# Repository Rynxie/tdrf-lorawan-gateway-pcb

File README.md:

# Open-Source Linux-Based LoRaWAN Gateway

A custom-designed, open-source **LoRaWAN gateway PCB** powered by the **Allwinner V3s ARM Cortex-A7 processor** and the **Semtech SX1302 LoRa concentrator**.

The gateway combines custom hardware with an embedded Linux software stack built using Buildroot, providing a flexible platform for LoRaWAN communication and IoT applications.

## Hardware Prototypes

Two assembled and tested LoRaWAN gateway prototypes.

| Assembled Gateway | PCB Component Layout |
|---|---|
|  |  |

## Project Overview

This project focuses on designing and developing a standalone Linux-based LoRaWAN gateway, including both custom PCB hardware and embedded Linux firmware.

The gateway was developed under the **TÜBİTAK 2209-A Undergraduate Research Projects Support Program** and subsequently integrated into the **LoRa-Based Low-Power Tracking System for Critical Cargo**, supported by the **Turkish Aerospace Industries LIFT UP Graduation Project Support Program**.

## Hardware

The hardware was designed in **KiCad**, integrating the processing unit, LoRa concentrator, RF transceivers, and peripheral interfaces on a custom PCB.

### Main Components

| Component | Description |
|---|---|
| Allwinner V3s | ARM Cortex-A7 MPU with integrated 64 MB DDR2 RAM |
| Semtech SX1302 | LoRa Core digital baseband concentrator |
| Semtech SX1250 | LoRa RF transceivers |
| Ethernet | Wired network connectivity |
| Quectel L86 | GNSS module |
| USB Type-C | USB interface |
| Custom PCB | Integrated gateway hardware platform |

## Embedded Linux Software

The gateway runs a customized embedded Linux distribution generated using **Buildroot**.

The software environment includes:

- **Linux Kernel:** Customized for the Allwinner V3s hardware platform
- **BusyBox:** Lightweight userspace utilities
- **Semtech UDP Packet Forwarder:** Forwarding LoRa packets to a network server
- **ChirpStack:** LoRaWAN Network Server integration

### System Architecture

```text
        LoRaWAN End Devices
                 |
                 | LoRa RF
                 v
       +-------------------+
       | Semtech SX1250    |
       | RF Transceivers   |
       +---------+---------+
                 |
                 v
       +-------------------+
       | Semtech SX1302    |
       | LoRa Concentrator |
       +---------+---------+
                 |
                 | SPI
                 v
       +-------------------+
       | Allwinner V3s     |
       | Embedded Linux    |
       | Buildroot         |
       | Packet Forwarder  |
       +---------+---------+
                 |
                 | Ethernet
                 v
       +-------------------+
       | ChirpStack        |
       | LoRaWAN Network   |
       | Server            |
       +-------------------+
```

## Testing and Validation

Two final hardware prototypes were manufactured, assembled, and tested.

The gateway was integrated into a LoRa-based low-power tracking system for critical cargo, providing a practical environment for evaluating the custom hardware and embedded Linux software.

We reached up to **1 km** distance in a urban area and looking for ways to increase the range

## Repository Contents

This repository focuses on the **hardware design** of the LoRaWAN gateway.

It contains the KiCad project and associated hardware design resources, including:

- PCB schematic
- PCB layout
- Component symbols and footprints
- Manufacturing and production files

## Project Team

- **Tunahan Kaya** — Embedded Linux and software development
- **Dilara Tatar** — Hardware development
- **Dr. Yalçın Albayrak** — Academic advisor

## Acknowledgments

This project was supported by the **TÜBİTAK 2209-A Undergraduate Research Projects Support Program**.

The gateway was also integrated and tested within a project supported by the **TUSAŞ LIFT UP Graduation Project Support Program**.

Special thanks to the project team and our academic advisor for their contributions and support throughout the development process.

## References

- [GitHub Repository](https://github.com/Rynxie/tdrf-lorawan-gateway-pcb)
- [Original LinkedIn Post](https://lnkd.in/p/d-5i6TTB)

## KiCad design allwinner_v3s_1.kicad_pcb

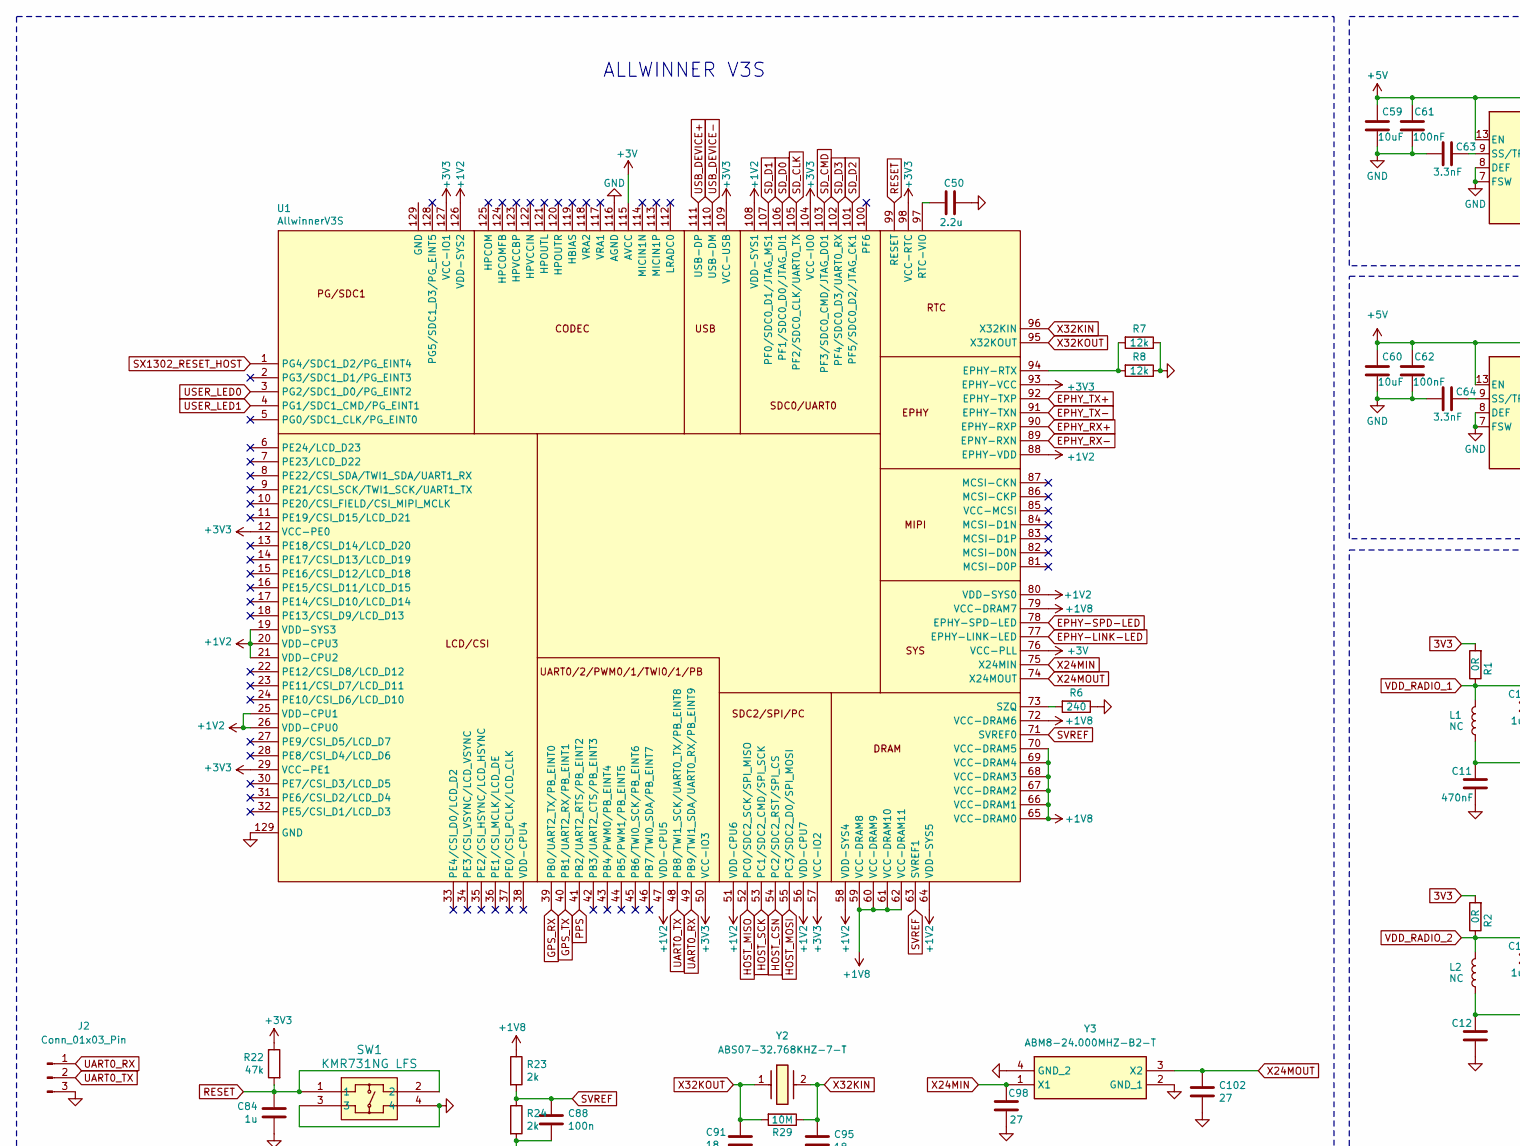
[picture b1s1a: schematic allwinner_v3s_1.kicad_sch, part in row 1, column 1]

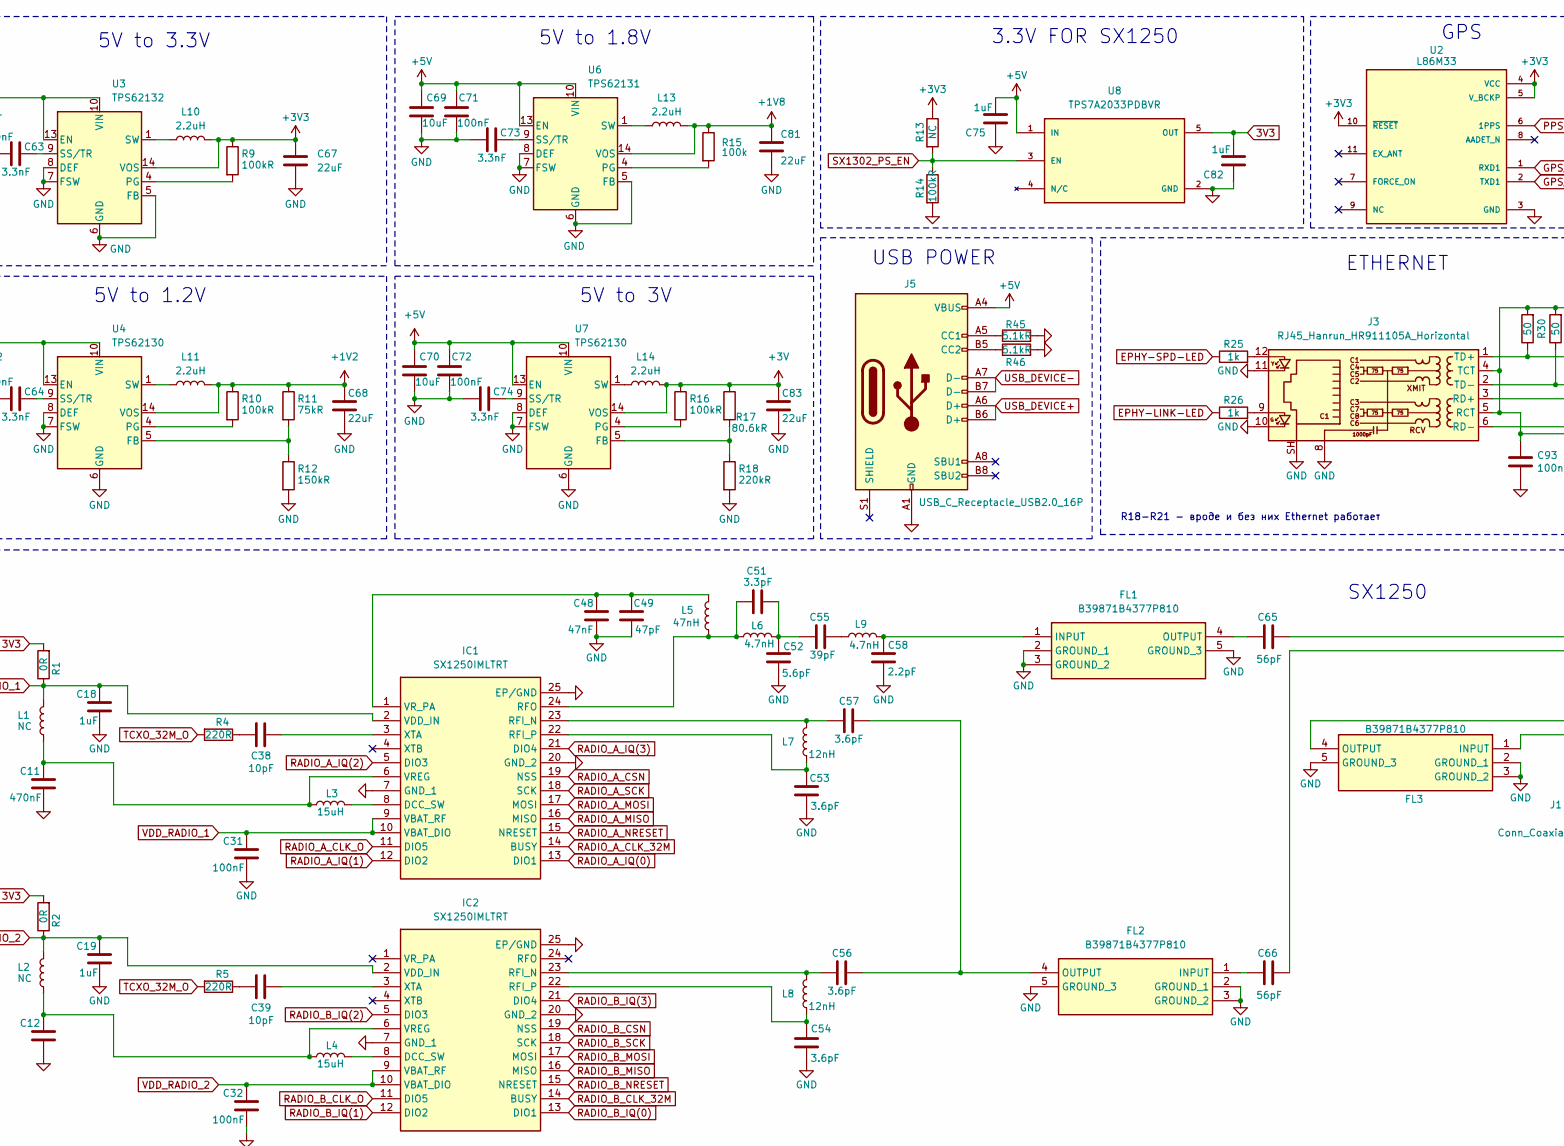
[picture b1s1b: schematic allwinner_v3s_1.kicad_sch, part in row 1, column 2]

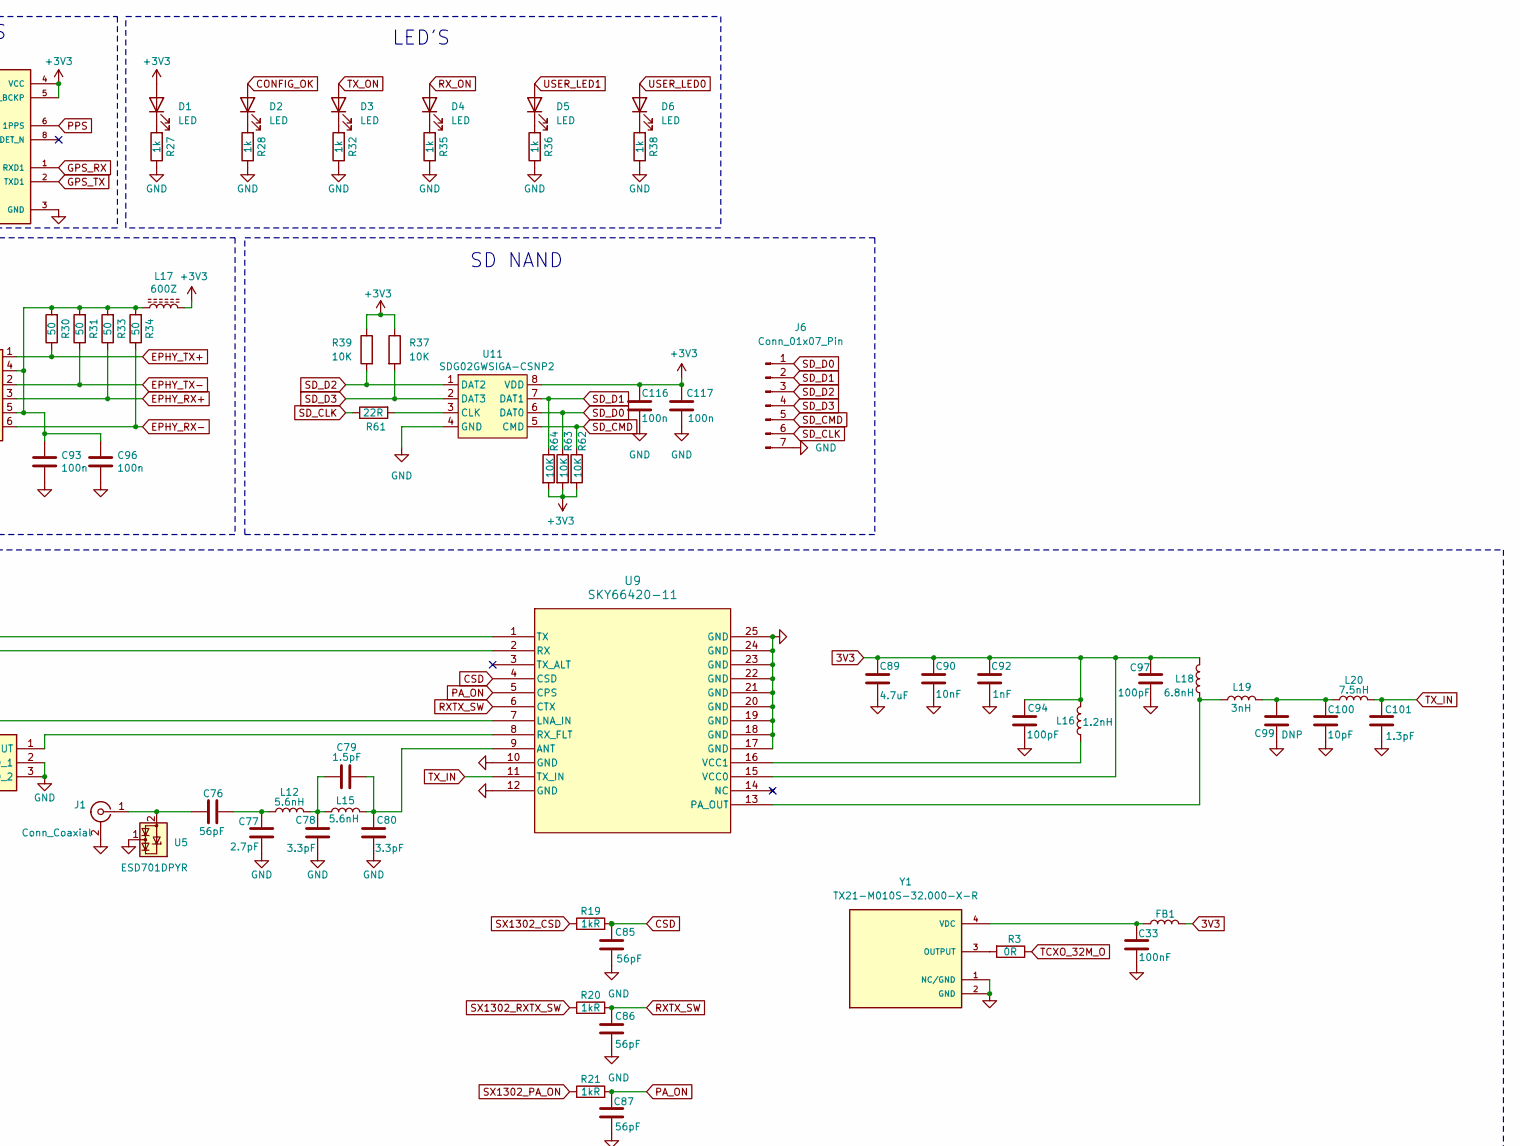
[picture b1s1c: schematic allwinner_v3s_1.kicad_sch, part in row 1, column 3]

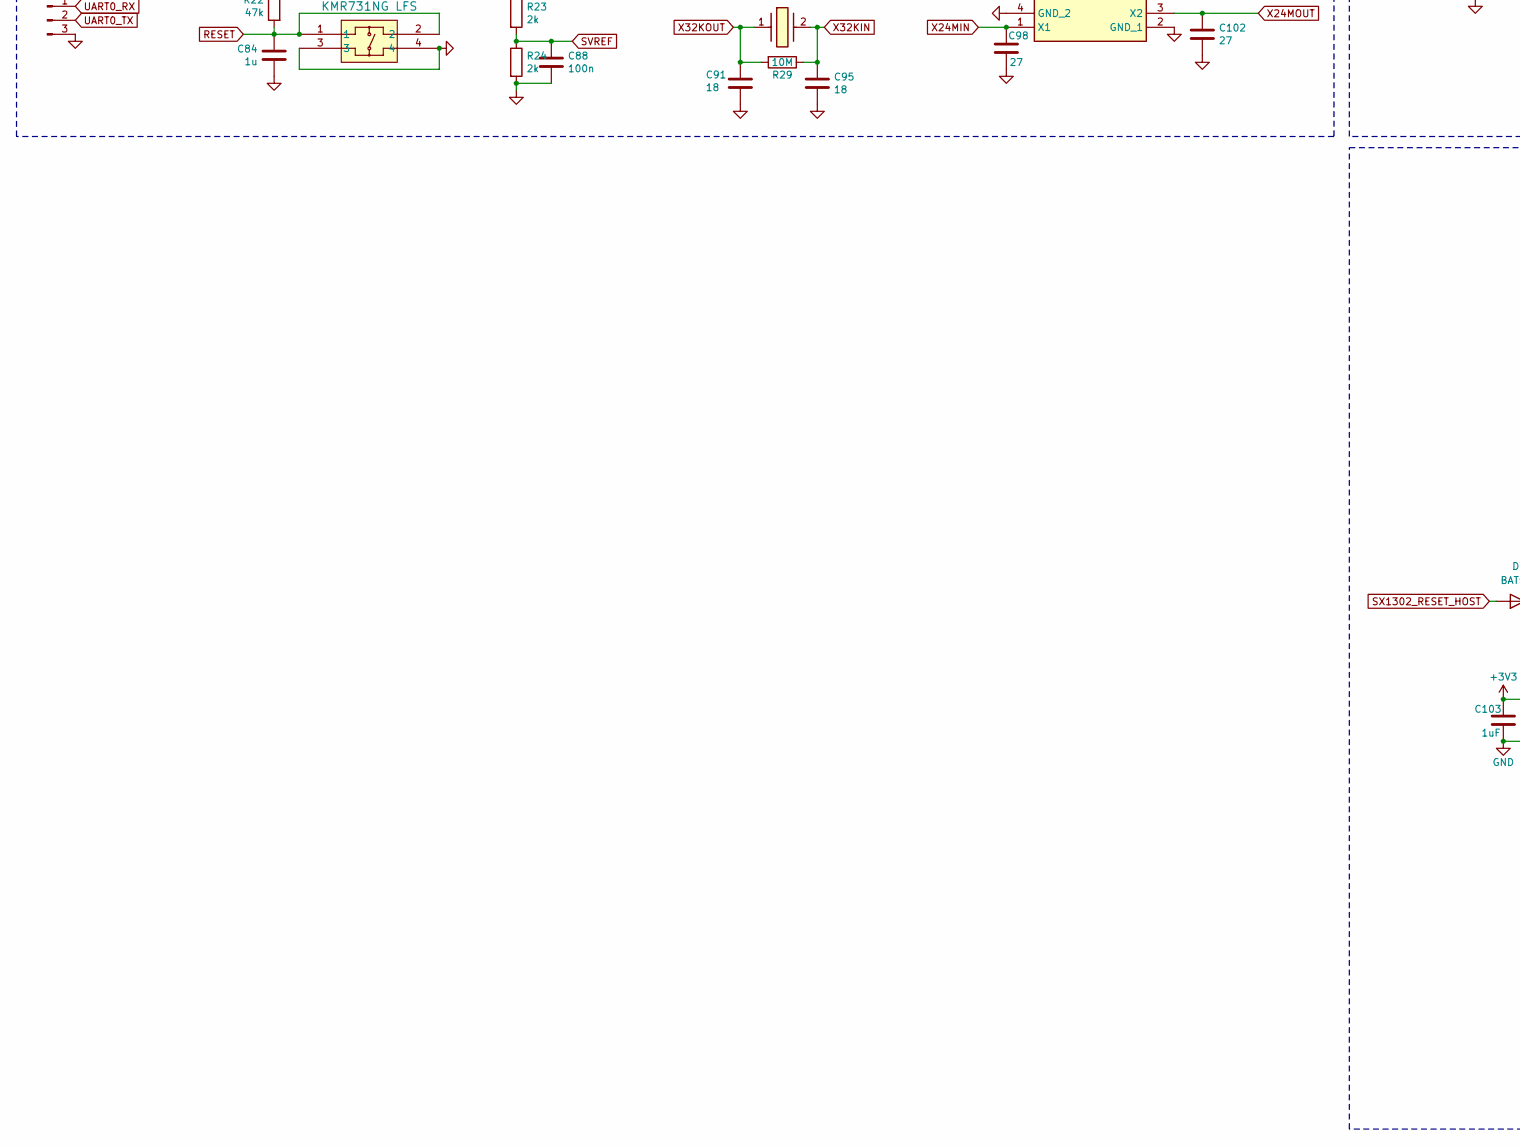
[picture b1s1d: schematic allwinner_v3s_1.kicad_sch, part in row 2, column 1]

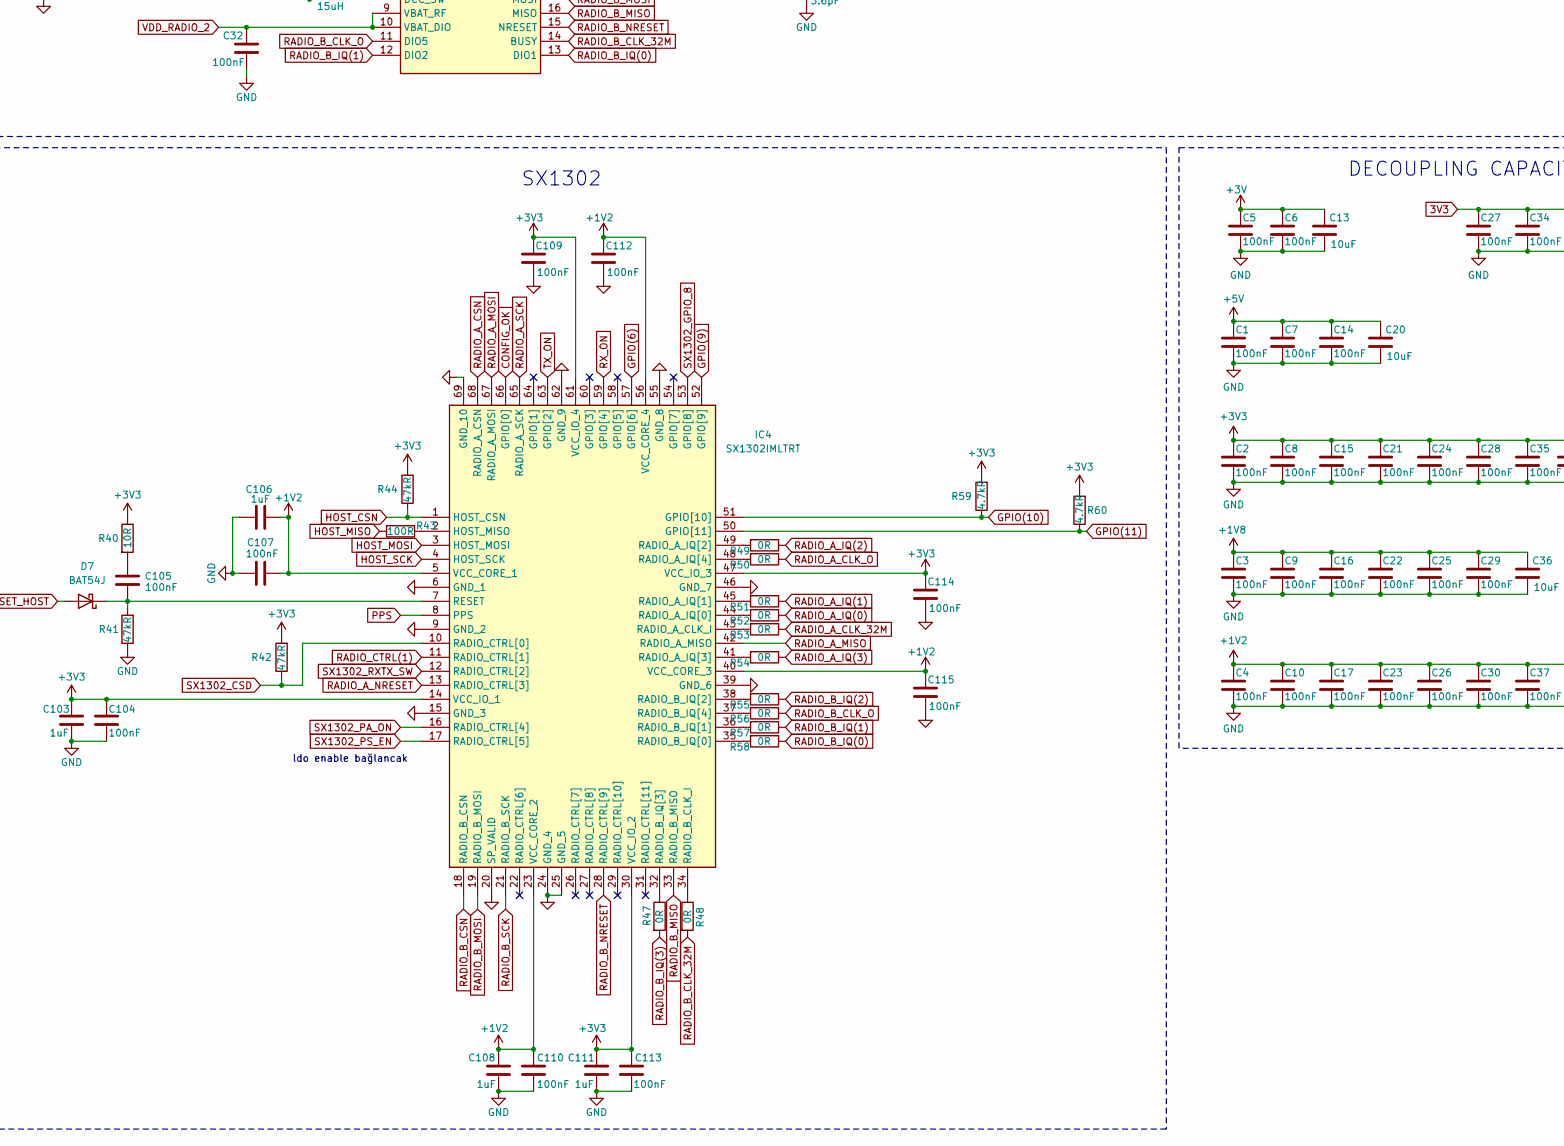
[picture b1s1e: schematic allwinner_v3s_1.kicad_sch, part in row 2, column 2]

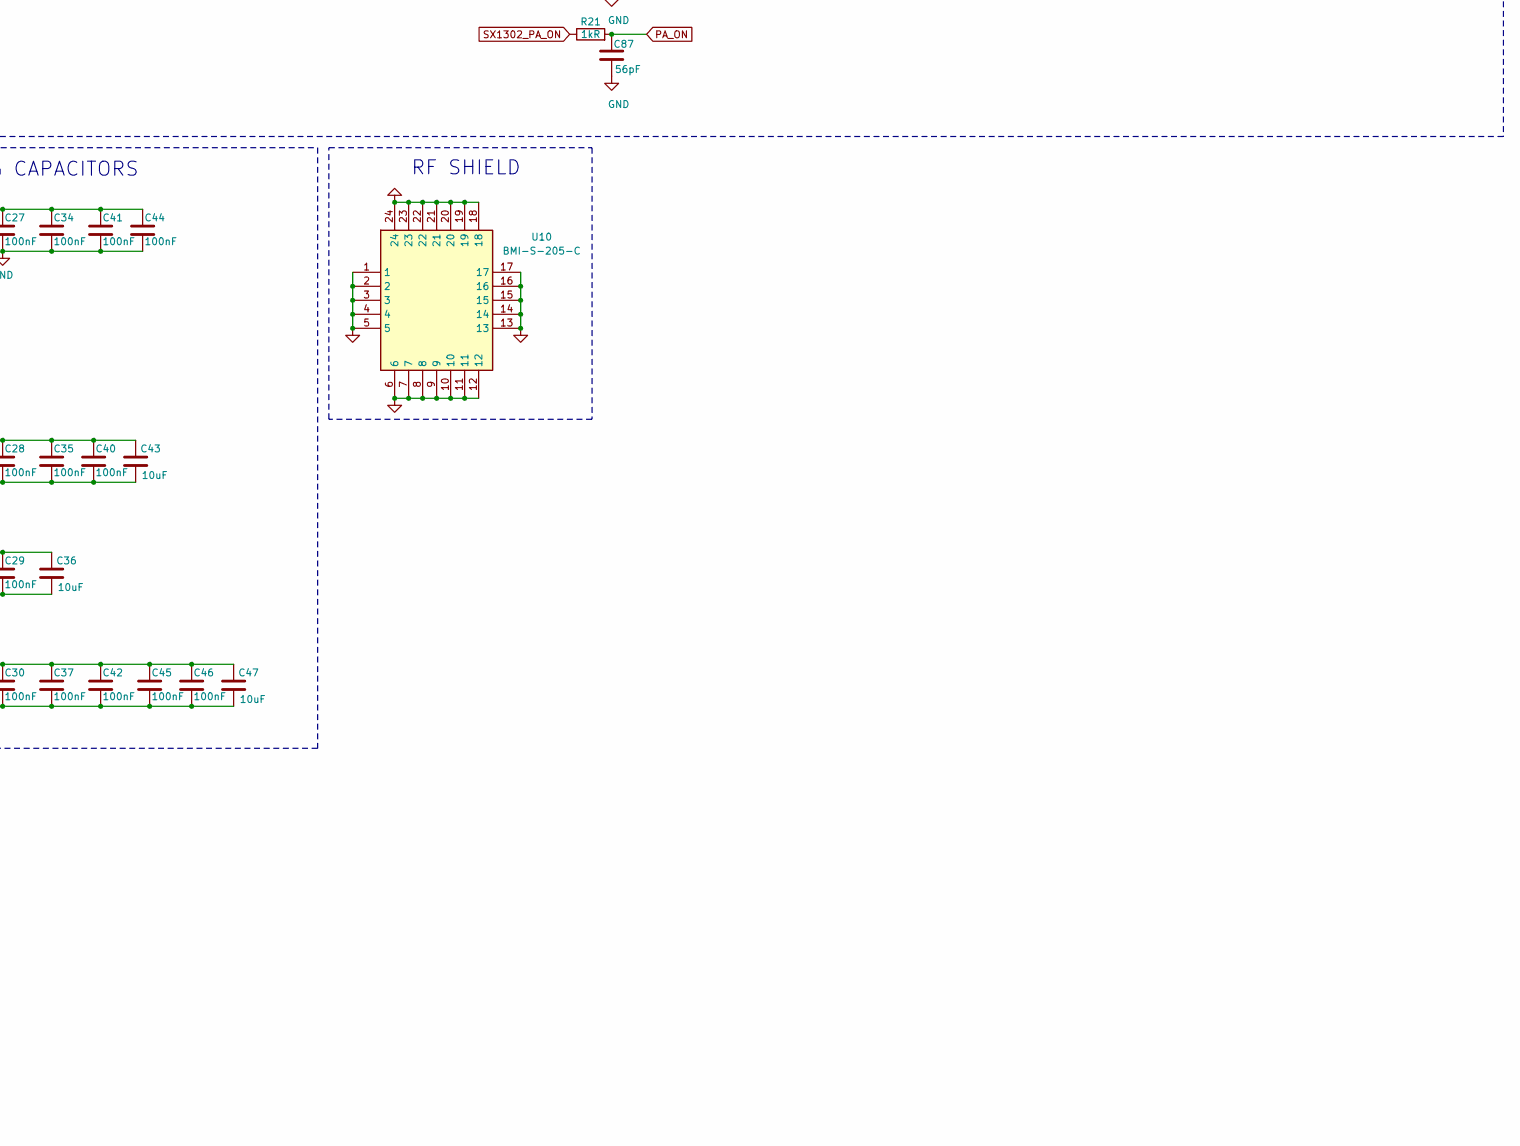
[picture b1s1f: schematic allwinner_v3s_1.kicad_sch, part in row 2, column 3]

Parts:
C1, C2, C3, C4, C5, C6, C7, C8, C9, C10, C14, C15, C16, C17, C21, C22, C23, C24, C25, C26, C27, C28, C29, C30, C32, C34, C35, C37, C40, C41, C42, C44, C45, C46, C104, C107, C109, C110, C112, C113, C114: 100nF; C_0201_0603Metric_Pad0.64x0.40mm_HandSolder
C11, C12: 470nF; C_0402_1005Metric_Pad0.74x0.62mm_HandSolder
C13, C20, C36, C43, C47, C59, C60, C69, C70: 10uF; C_0603_1608Metric_Pad1.08x0.95mm_HandSolder
C18, C19, C75, C82, C103, C106, C108, C111: 1uF; C_0402_1005Metric_Pad0.74x0.62mm_HandSolder
C31, C33, C61, C62, C71, C72, C115: 100nF; C_0402_1005Metric_Pad0.74x0.62mm_HandSolder
C38, C39, C100: 10pF; C_0201_0603Metric_Pad0.64x0.40mm_HandSolder
C48: 47nF; C_0402_1005Metric_Pad0.74x0.62mm_HandSolder
C49: 47pF; C_0201_0603Metric_Pad0.64x0.40mm_HandSolder
C50: 2.2u; C_0603_1608Metric_Pad1.08x0.95mm_HandSolder
C51, C78, C80: 3.3pF; C_0201_0603Metric_Pad0.64x0.40mm_HandSolder
C52: 5.6pF; C_0201_0603Metric_Pad0.64x0.40mm_HandSolder
C53, C54, C56, C57: 3.6pF; C_0201_0603Metric_Pad0.64x0.40mm_HandSolder
C55: 39pF; C_0201_0603Metric_Pad0.64x0.40mm_HandSolder
C58: 2.2pF; C_0201_0603Metric_Pad0.64x0.40mm_HandSolder
C63, C64, C73, C74: 3.3nF; C_0402_1005Metric_Pad0.74x0.62mm_HandSolder
C65, C66, C76: 56pF; C_0201_0603Metric_Pad0.64x0.40mm_HandSolder
C67, C68, C81, C83: 22uF; C_0805_2012Metric_Pad1.18x1.45mm_HandSolder
C77: 2.7pF; C_0201_0603Metric_Pad0.64x0.40mm_HandSolder
C79: 1.5pF; C_0201_0603Metric_Pad0.64x0.40mm_HandSolder
C84: 1u; C_0603_1608Metric
C85, C86, C87: 56pF; C_0201_0603Metric
C88: 100n; C_0201_0603Metric_Pad0.64x0.40mm_HandSolder
C89: 4.7uF; C_0603_1608Metric_Pad1.08x0.95mm_HandSolder
C90: 10nF; C_0402_1005Metric_Pad0.74x0.62mm_HandSolder
C91, C95: 18; C_0402_1005Metric_Pad0.74x0.62mm_HandSolder
C92: 1nF; C_0402_1005Metric_Pad0.74x0.62mm_HandSolder
C93, C96: 100n; C_0402_1005Metric_Pad0.74x0.62mm_HandSolder
C94, C97: 100pF; C_0402_1005Metric_Pad0.74x0.62mm_HandSolder
C98, C102: 27; C_0402_1005Metric_Pad0.74x0.62mm_HandSolder
C99: DNP; C_0201_0603Metric_Pad0.64x0.40mm_HandSolder
C101: 1.3pF; C_0201_0603Metric_Pad0.64x0.40mm_HandSolder
C105: 100nF; R_0201_0603Metric_Pad0.64x0.40mm_HandSolder
C116, C117: 100n; C_0201_0603Metric
D1, D2, D3, D4, D5, D6: LED; LED_0805_2012Metric_Pad1.15x1.40mm_HandSolder
D7: BAT54J; D_SOD-323F
FB1: BLM15PG100SN1D; L_0402_1005Metric_Pad0.77x0.64mm_HandSolder
FL1, FL2, FL3: B39871B4377P810; Manufacturer_Part_Number B39871B4377P810; Mouser Part Number 871-B39871B4377P810
IC1, IC2: SX1250IMLTRT; QFN50P400X400X100-25N-D; Manufacturer_Part_Number SX1250IMLTRT; Mouser Part Number 947-SX1250IMLTRT
IC4: SX1302IMLTRT; QFN35P700X700X80-69N-D; Manufacturer_Part_Number SX1302IMLTRT; Mouser Part Number 947-SX1302IMLTRT
J1: Conn_Coaxial; TE_CONSMA020.062-G
J2: Conn_01x03_Pin; PinHeader_1x03_P2.54mm_Vertical
J3: RJ45_Hanrun_HR911105A_Horizontal
J5: USB_C_Receptacle_USB2.0_16P; USB_C_Receptacle_GCT_USB4105-xx-A_16P_TopMnt_Horizontal
J6: Conn_01x07_Pin; PinHeader_1x07_P2.54mm_Vertical
L1, L2: NC; L_0402_1005Metric_Pad0.77x0.64mm_HandSolder
L3, L4: 15uH; L_0805_2012Metric_Pad1.05x1.20mm_HandSolder
L5: 47nH; L_0402_1005Metric_Pad0.77x0.64mm_HandSolder
L6, L9: 4.7nH; L_0402_1005Metric_Pad0.77x0.64mm_HandSolder
L7, L8: 12nH; L_0402_1005Metric_Pad0.77x0.64mm_HandSolder
L10, L11, L13, L14: 2.2uH; L_Coilcraft_XAL4020-XXX
L12: 5.6nH; C_0402_1005Metric
L15: 5.6nH; L_0402_1005Metric_Pad0.77x0.64mm_HandSolder
L16: 1.2nH; L_0402_1005Metric_Pad0.77x0.64mm_HandSolder
L17: 600Z; L_1206_3216Metric
L18: 6.8nH; L_0402_1005Metric_Pad0.77x0.64mm_HandSolder
L19: 3nH; L_0402_1005Metric_Pad0.77x0.64mm_HandSolder
L20: 7.5nH; L_0402_1005Metric_Pad0.77x0.64mm_HandSolder
R1, R2, R3: 0R; R_0402_1005Metric_Pad0.72x0.64mm_HandSolder
R4: 220R; C_0201_0603Metric_Pad0.64x0.40mm_HandSolder
R5: 220R; R_0201_0603Metric_Pad0.64x0.40mm_HandSolder
R6: 240; R_0201_0603Metric_Pad0.64x0.40mm_HandSolder
R7, R8: 12k; R_0201_0603Metric_Pad0.64x0.40mm_HandSolder
R9, R10, R16: 100kR; R_0201_0603Metric_Pad0.64x0.40mm_HandSolder
R11: 75kR; R_0201_0603Metric_Pad0.64x0.40mm_HandSolder
R12: 150kR; R_0201_0603Metric_Pad0.64x0.40mm_HandSolder
R13: NC; R_0402_1005Metric_Pad0.72x0.64mm_HandSolder
R14: 100kR; R_0402_1005Metric_Pad0.72x0.64mm_HandSolder
R15: 100k; R_0201_0603Metric_Pad0.64x0.40mm_HandSolder
R17: 80.6kR; R_0201_0603Metric_Pad0.64x0.40mm_HandSolder
R18: 220kR; R_0201_0603Metric_Pad0.64x0.40mm_HandSolder
R19, R20, R21: 1kR; R_0201_0603Metric
R22: 47k; R_0201_0603Metric_Pad0.64x0.40mm_HandSolder
R23, R24: 2k; R_0201_0603Metric_Pad0.64x0.40mm_HandSolder
R25, R26, R27, R28, R32, R35, R36, R38: 1k; R_0402_1005Metric_Pad0.72x0.64mm_HandSolder
R29: 10M; R_0201_0603Metric_Pad0.64x0.40mm_HandSolder
R30, R31, R33, R34: 50; R_0201_0603Metric_Pad0.64x0.40mm_HandSolder
R37, R39, R62, R63, R64: 10K; R_0201_0603Metric
R40: 10R; R_0402_1005Metric_Pad0.72x0.64mm_HandSolder
R41, R42, R44: 47kR; R_0201_0603Metric_Pad0.64x0.40mm_HandSolder
R43: 100R; R_0201_0603Metric
R45, R46: 5.1kR; R_0201_0603Metric_Pad0.64x0.40mm_HandSolder
R47, R48, R49, R50, R51, R52, R53, R54, R55, R56, R57, R58: 0R; R_0201_0603Metric_Pad0.64x0.40mm_HandSolder
R59, R60: 4.7kR; R_0201_0603Metric_Pad0.64x0.40mm_HandSolder
R61: 22R; R_0201_0603Metric
SW1: KMR731NG LFS; KMR7_CNK
U1: AllwinnerV3S; QFP40P1600X1600X160-129N
U2: L86M33; XCVR_L86M33
U3: TPS62132; VQFN-16-1EP_3x3mm_P0.5mm_EP1.68x1.68mm_ThermalVias
U4, U7: TPS62130; VQFN-16-1EP_3x3mm_P0.5mm_EP1.68x1.68mm_ThermalVias
U5: ESD701DPYR; Texas_DPY0002A_0.6x1mm_P0.65mm
U6: TPS62131; VQFN-16-1EP_3x3mm_P0.5mm_EP1.68x1.68mm_ThermalVias
U8: TPS7A2033PDBVR; SOT95P280X145-5N; PARTREV H
U9: SKY66420-11; MCM16_3X3X0P75_SKY
U10: BMI-S-205-C; shield; Manufacturer_Part_Number BMI-S-205-C; Mouser Part Number 739-BMI-205-C
U11: SDG02GWSIGA-CSNP2; SDTRUVAL_SDG02GWSIGA-CSNP2
Y1: TX21-M010S-32.000-X-R; OSC_TX21-M010S-32.000-X-R; PARTREV Nov 07, 2023; DigiKey_Part_Number 3997-TX21-M010S-32.000-X-RCT-ND
Y2: ABS07-32.768KHZ-7-T; ABS07; Manufacturer_Part_Number ABS07-32.768KHZ-7-T; Mouser Part Number 815-ABS07-32.768K7T
Y3: ABM8-24.000MHZ-B2-T; ABM810000MHZ12D2W; Manufacturer_Part_Number ABM8-24.000MHZ-B2-T; Mouser Part Number 815-ABM8-24-B2-T

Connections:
3V3: C27.1, C34.1, C41.1, C44.1, C82.2, C89.2, C90.2, C92.1, C94.1, C97.1, FB1.2, L16.2, L18.2, R1.2, R2.2, U8.5 (OUT), U9.15 (VCC0)
+1V2: C4.1, C10.1, C17.1, C23.1, C26.1, C30.1, C37.1, C42.1, C45.1, C46.1, C47.1, C68.1, C106.2, C107.2, C108.2, C110.2, C112.2, C115.2, IC4.5 (VCC_CORE_1), IC4.23 (VCC_CORE_2), IC4.40 (VCC_CORE_3), IC4.56 (VCC_CORE_4), L11.2, R10.1, R11.1, U1.19 (VDD-SYS3), U1.20 (VDD-CPU3), U1.21 (VDD-CPU2), U1.25 (VDD-CPU1), U1.26 (VDD-CPU0), U1.47 (VDD-CPU5), U1.51 (VDD-CPU6), U1.56 (VDD-CPU7), U1.58 (VDD-SYS4), U1.64 (VDD-SYS5), U1.80 (VDD-SYS0), U1.88 (EPHY-VDD), U1.108 (VDD-SYS1), U1.126 (VDD-SYS2), U4.14 (VOS)
+1V8: C3.1, C9.1, C16.1, C22.1, C25.1, C29.1, C36.1, C81.1, L13.2, R15.1, R23.1, U1.59 (VCC-DRAM8), U1.60 (VCC-DRAM9), U1.61 (VCC-DRAM10), U1.62 (VCC-DRAM11), U1.65 (VCC-DRAM0), U1.66 (VCC-DRAM1), U1.67 (VCC-DRAM2), U1.68 (VCC-DRAM3), U1.69 (VCC-DRAM4), U1.70 (VCC-DRAM5), U1.72 (VCC-DRAM6), U1.79 (VCC-DRAM7), U6.14 (VOS)
+3V: C5.1, C6.1, C13.1, C83.1, L14.2, R16.1, R17.1, U1.76 (VCC-PLL), U1.115 (AVCC), U7.14 (VOS)
+3V3: C2.1, C8.1, C15.1, C21.1, C24.1, C28.1, C35.1, C40.1, C43.1, C67.1, C103.2, C104.2, C109.2, C111.2, C113.2, C114.2, C116.1, C117.1, D1.2 (A), IC4.14 (VCC_IO_1), IC4.30 (VCC_IO_2), IC4.47 (VCC_IO_3), IC4.61 (VCC_IO_4), L10.2, L17.2, R9.1, R13.1, R22.1, R37.1, R39.1, R40.1, R42.2, R44.2, R59.2, R60.2, R62.2, R63.2, R64.2, U1.12 (VCC-PE0), U1.29 (VCC-PE1), U1.50 (VCC-IO3), U1.57 (VCC-IO2), U1.93 (EPHY-VCC), U1.98 (VCC-RTC), U1.104 (VCC-IO0), U1.109 (VCC-USB), U1.127 (VCC-IO1), U2.4 (VCC), U2.5 (V_BCKP), U2.10 (~RESET), U3.14 (VOS), U11.8 (VDD)
+5V: C1.1, C7.1, C14.1, C20.1, C59.2, C60.2, C61.1, C62.1, C69.2, C70.2, C71.1, C72.1, C75.2, J5.A4 (VBUS), J5.A9 (VBUS), J5.B4 (VBUS), J5.B9 (VBUS), U3.10 (VIN), U3.11 (VIN), U3.12 (VIN), U3.13 (EN), U4.10 (VIN), U4.11 (VIN), U4.12 (VIN), U4.13 (EN), U6.10 (VIN), U6.11 (VIN), U6.12 (VIN), U6.13 (EN), U7.10 (VIN), U7.11 (VIN), U7.12 (VIN), U7.13 (EN), U8.1 (IN)
CONFIG_OK: D2.2 (A), IC4.66 (GPIO[0])
CSD: C85.1, R19.2, U9.4 (CSD)
EPHY-LINK-LED: R26.1, U1.77 (EPHY-LINK-LED)
EPHY-SPD-LED: R25.1, U1.78 (EPHY-SPD-LED)
EPHY_RX+: J3.3 (RD+), R33.1, U1.90 (EPHY-RXP)
EPHY_RX-: J3.6 (RD-), R34.1, U1.89 (EPNY-RXN)
EPHY_TX+: J3.1 (TD+), R30.1, U1.92 (EPHY-TXP)
EPHY_TX-: J3.2 (TD-), R31.1, U1.91 (EPHY-TXN)
GND: C1.2, C2.2, C3.2, C4.2, C5.2, C6.2, C7.2, C8.2, C9.2, C10.2, C11.1, C12.1, C13.2, C14.2, C15.2, C16.2, C17.2, C18.1, C19.1, C20.2, C21.2, C22.2, C23.2, C24.2, C25.2, C26.2, C27.2, C28.2, C29.2, C30.2, C31.1, C32.1, C33.1, C34.2, C35.2, C36.2, C37.2, C40.2, C41.2, C42.2, C43.2, C44.2, C45.2, C46.2, C47.2, C48.1, C49.1, C50.2, C52.1, C53.2, C54.2, C58.2, C59.1, C60.1, C61.2, C62.2, C63.1, C64.1, C67.2, C68.2, C69.1, C70.1, C71.2, C72.2, C73.1, C74.1, C75.1, C77.2, C78.1, C80.1, C81.2, C82.1, C83.2, C84.2, C85.2, C86.2, C87.2, C88.2, C89.1, C90.1, C91.2, C92.2, C93.2, C94.2, C95.2, C96.2, C97.2, C98.2, C99.2, C100.1, C101.2, C102.2, C103.1, C104.1, C106.1, C107.1, C108.1, C109.1, C110.1, C111.1, C112.1, C113.1, C114.1, C115.1, C116.2, C117.2, FL1.2 (GROUND_1), FL1.3 (GROUND_2), FL1.5 (GROUND_3), FL2.2 (GROUND_1), FL2.3 (GROUND_2), FL2.5 (GROUND_3), FL3.2 (GROUND_1), FL3.3 (GROUND_2), FL3.5 (GROUND_3), IC1.7 (GND_1), IC1.20 (GND_2), IC1.25 (EP/GND), IC2.7 (GND_1), IC2.20 (GND_2), IC2.25 (EP/GND), IC4.6 (GND_1), IC4.9 (GND_2), IC4.15 (GND_3), IC4.20 (SP_VALID), IC4.24 (GND_4), IC4.25 (GND_5), IC4.39 (GND_6), IC4.46 (GND_7), IC4.55 (GND_8), IC4.62 (GND_9), IC4.69 (GND_10), J1.2 (Ext), J2.3, J3.8, J3.10, J3.11, J3.SH, J5.A1 (GND), J5.A12 (GND), J5.B1 (GND), J5.B12 (GND), J6.7, R6.1, R7.1, R8.1, R12.2, R14.2, R18.2, R24.2, R27.1, R28.1, R32.1, R35.1, R36.1, R38.1, R41.1, R45.2, R46.2, SW1.3, SW1.4, U1.116 (AGND), U1.129 (GND), U2.3 (GND), U2.12 (GND), U3.5 (FB), U3.6 (GND), U3.7 (FSW), U3.8 (DEF), U3.15 (GND), U3.16 (GND), U3.17 (GND), U4.6 (GND), U4.7 (FSW), U4.8 (DEF), U4.15 (GND), U4.16 (GND), U4.17 (GND), U5.1 (I/O), U6.5 (FB), U6.6 (GND), U6.7 (FSW), U6.8 (DEF), U6.15 (GND), U6.16 (GND), U6.17 (GND), U7.6 (GND), U7.7 (FSW), U7.8 (DEF), U7.15 (GND), U7.16 (GND), U7.17 (GND), U8.2 (GND), U9.10 (GND), U9.12 (GND), U9.17 (GND), U9.18 (GND), U9.19 (GND), U9.20 (GND), U9.21 (GND), U9.22 (GND), U9.23 (GND), U9.24 (GND), U9.25 (GND), U10.1, U10.2, U10.3, U10.4, U10.5, U10.6, U10.7, U10.8, U10.9, U10.10, U10.11, U10.12, U10.13, U10.14, U10.15, U10.16, U10.17, U10.18, U10.19, U10.20, U10.21, U10.22, U10.23, U10.24, U11.4 (GND), Y1.1 (NC/GND), Y1.2 (GND), Y3.2 (GND_1), Y3.4 (GND_2)
GPIO(6): IC4.57 (GPIO[6])
GPIO(9): IC4.52 (GPIO[9])
GPIO(10): IC4.51 (GPIO[10]), R59.1
GPIO(11): IC4.50 (GPIO[11]), R60.1
GPS_RX: U1.39 (PB0/UART2_TX/PB_EINT0), U2.1 (RXD1)
GPS_TX: U1.40 (PB1/UART2_RX/PB_EINT1), U2.2 (TXD1)
HOST_CSN: IC4.1 (HOST_CSN), R44.1, U1.54 (PC2/SDC2_RST/SPI_CS)
HOST_MISO: R43.2, U1.52 (PC0/SDC2_SCK/SPI_MISO)
HOST_MOSI: IC4.3 (HOST_MOSI), U1.55 (PC3/SDC2_D0/SPI_MOSI)
HOST_SCK: IC4.4 (HOST_SCK), U1.53 (PC1/SDC2_CMD/SPI_SCK)
unnamed: C38.2, R4.1
unnamed: C39.2, R5.1
unnamed: C51.1, C52.2, C55.2, L6.2
unnamed: C55.1, L9.1
unnamed: C76.1, C77.1, L12.2
unnamed: C78.2, C79.1, L12.1, L15.2
unnamed: C99.1, C100.2, L19.2, L20.1
unnamed: C105.2, R40.2
unnamed: D1.1 (K), R27.2
unnamed: D2.1 (K), R28.2
unnamed: D3.1 (K), R32.2
unnamed: D4.1 (K), R35.2
unnamed: D5.1 (K), R36.2
unnamed: D6.1 (K), R38.2
unnamed: C105.1, D7.1 (K), IC4.7 (RESET), R41.2
unnamed: C58.1, FL1.1 (INPUT), L9.2
unnamed: C65.2, FL1.4 (OUTPUT)
unnamed: C66.2, FL2.1 (INPUT)
unnamed: C56.1, C57.1, FL2.4 (OUTPUT)
unnamed: FL3.1 (INPUT), U9.8 (RX_FLT)
unnamed: FL3.4 (OUTPUT), U9.7 (LNA_IN)
unnamed: IC1.8 (DCC_SW), L3.2
unnamed: C57.2, IC1.23 (RFI_N), L7.2
unnamed: C53.1, IC1.22 (RFI_P), L7.1
unnamed: C51.2, IC1.24 (RFO), L5.1, L6.1
unnamed: C11.2, IC1.6 (VREG), L1.1, L3.1
unnamed: C48.2, C49.2, IC1.1 (VR_PA), L5.2
unnamed: C38.1, IC1.3 (XTA)
unnamed: IC2.8 (DCC_SW), L4.2
unnamed: C56.2, IC2.23 (RFI_N), L8.2
unnamed: C54.1, IC2.22 (RFI_P), L8.1
unnamed: C12.2, IC2.6 (VREG), L2.1, L4.1
unnamed: C39.1, IC2.3 (XTA)
unnamed: IC4.2 (HOST_MISO), R43.1
unnamed: IC4.43 (RADIO_A_CLK_I), R53.2
unnamed: IC4.44 (RADIO_A_IQ[0]), R52.2
unnamed: IC4.45 (RADIO_A_IQ[1]), R51.2
unnamed: IC4.49 (RADIO_A_IQ[2]), R49.2
unnamed: IC4.41 (RADIO_A_IQ[3]), R54.2
unnamed: IC4.48 (RADIO_A_IQ[4]), R50.2
unnamed: IC4.34 (RADIO_B_CLK_I), R48.1
unnamed: IC4.35 (RADIO_B_IQ[0]), R58.2
unnamed: IC4.36 (RADIO_B_IQ[1]), R57.2
unnamed: IC4.38 (RADIO_B_IQ[2]), R55.2
unnamed: IC4.32 (RADIO_B_IQ[3]), R47.1
unnamed: IC4.37 (RADIO_B_IQ[4]), R56.2
unnamed: C76.2, J1.1 (In), U5.2 (GND)
unnamed: J3.9, R26.2
unnamed: J3.12, R25.2
unnamed: C93.1, C96.1, J3.4 (TCT), J3.5 (RCT), L17.1, R30.2, R31.2, R33.2, R34.2
unnamed: J5.A5 (CC1), R45.1
unnamed: J5.B5 (CC2), R46.1
unnamed: L10.1, U3.1 (SW), U3.2 (SW), U3.3 (SW)
unnamed: L11.1, U4.1 (SW), U4.2 (SW), U4.3 (SW)
unnamed: L13.1, U6.1 (SW), U6.2 (SW), U6.3 (SW)
unnamed: L14.1, U7.1 (SW), U7.2 (SW), U7.3 (SW)
unnamed: R7.2, R8.2, U1.94 (EPHY-RTX)
unnamed: C50.1, U1.97 (RTC-VIO)
unnamed: R6.2, U1.73 (SZQ)
unnamed: R9.2, U3.4 (PG)
unnamed: C63.2, U3.9 (SS/TR)
unnamed: R11.2, R12.1, U4.5 (FB)
unnamed: R10.2, U4.4 (PG)
unnamed: C64.2, U4.9 (SS/TR)
unnamed: R15.2, U6.4 (PG)
unnamed: C73.2, U6.9 (SS/TR)
unnamed: R17.2, R18.1, U7.5 (FB)
unnamed: R16.2, U7.4 (PG)
unnamed: C74.2, U7.9 (SS/TR)
unnamed: C79.2, C80.2, L15.1, U9.9 (ANT)
unnamed: L18.1, L19.1, U9.13 (PA_OUT)
unnamed: C66.1, U9.2 (RX)
unnamed: C65.1, U9.1 (TX)
unnamed: L16.1, U9.16 (VCC1)
unnamed: R61.2, U11.3 (CLK)
unnamed: R3.2, Y1.3 (OUTPUT)
unnamed: C33.2, FB1.1, Y1.4 (VDC)
PA_ON: C87.1, R21.2, U9.5 (CPS)
PPS: IC4.8 (PPS), U1.41 (PB2/UART2_RTS/PB_EINT2), U2.6 (1PPS)
RADIO_A_CLK_32M: IC1.14 (BUSY), R53.1
RADIO_A_CLK_O: IC1.11 (DIO5), R50.1
RADIO_A_CSN: IC1.19 (NSS), IC4.68 (RADIO_A_CSN)
RADIO_A_IQ(0): IC1.13 (DIO1), R52.1
RADIO_A_IQ(1): IC1.12 (DIO2), R51.1
RADIO_A_IQ(2): IC1.5 (DIO3), R49.1
RADIO_A_IQ(3): IC1.21 (DIO4), R54.1
RADIO_A_MISO: IC1.16 (MISO), IC4.42 (RADIO_A_MISO)
RADIO_A_MOSI: IC1.17 (MOSI), IC4.67 (RADIO_A_MOSI)
RADIO_A_NRESET: IC1.15 (NRESET), IC4.13 (RADIO_CTRL[3])
RADIO_A_SCK: IC1.18 (SCK), IC4.65 (RADIO_A_SCK)
RADIO_B_CLK_32M: IC2.14 (BUSY), R48.2
RADIO_B_CLK_O: IC2.11 (DIO5), R56.1
RADIO_B_CSN: IC2.19 (NSS), IC4.18 (RADIO_B_CSN)
RADIO_B_IQ(0): IC2.13 (DIO1), R58.1
RADIO_B_IQ(1): IC2.12 (DIO2), R57.1
RADIO_B_IQ(2): IC2.5 (DIO3), R55.1
RADIO_B_IQ(3): IC2.21 (DIO4), R47.2
RADIO_B_MISO: IC2.16 (MISO), IC4.33 (RADIO_B_MISO)
RADIO_B_MOSI: IC2.17 (MOSI), IC4.19 (RADIO_B_MOSI)
RADIO_B_NRESET: IC2.15 (NRESET), IC4.28 (RADIO_CTRL[9])
RADIO_B_SCK: IC2.18 (SCK), IC4.21 (RADIO_B_SCK)
RADIO_CTRL(1): IC4.11 (RADIO_CTRL[1])
RESET: C84.1, R22.2, SW1.1, SW1.2, U1.99 (RESET)
RXTX_SW: C86.1, R20.2, U9.6 (CTX)
RX_ON: D4.2 (A), IC4.59 (GPIO[4])
SD_CLK: J6.6, R61.1, U1.105 (PF2/SDC0_CLK/UART0_TX)
SD_CMD: J6.5, R62.1, U1.103 (PF3/SDC0_CMD/JTAG_DO1), U11.5 (CMD)
SD_D0: J6.1, R63.1, U1.106 (PF1/SDC0_D0/JTAG_DI1), U11.6 (DAT0)
SD_D1: J6.2, R64.1, U1.107 (PF0/SDC0_D1/JTAG_MS1), U11.7 (DAT1)
SD_D2: J6.3, R39.2, U1.101 (PF5/SDC0_D2/JTAG_CK1), U11.1 (DAT2)
SD_D3: J6.4, R37.2, U1.102 (PF4/SDC0_D3/UART0_RX), U11.2 (DAT3)
SVREF: C88.1, R23.2, R24.1, U1.63 (SVREF1), U1.71 (SVREF0)
SX1302_CSD: IC4.10 (RADIO_CTRL[0]), R19.1, R42.1
SX1302_GPIO_8: IC4.53 (GPIO[8])
SX1302_PA_ON: IC4.16 (RADIO_CTRL[4]), R21.1
SX1302_PS_EN: IC4.17 (RADIO_CTRL[5]), R13.2, R14.1, U8.3 (EN)
SX1302_RESET_HOST: D7.2 (A), U1.1 (PG4/SDC1_D2/PG_EINT4)
SX1302_RXTX_SW: IC4.12 (RADIO_CTRL[2]), R20.1
TCXO_32M_O: R3.1, R4.2, R5.2
TX_IN: C101.1, L20.2, U9.11 (TX_IN)
TX_ON: D3.2 (A), IC4.63 (GPIO[2])
UART0_RX: J2.1, U1.49 (PB9/TWI1_SDA/UART0_RX/PB_EINT9)
UART0_TX: J2.2, U1.48 (PB8/TWI1_SCK/UART0_TX/PB_EINT8)
USB_DEVICE+: J5.A6 (D+), J5.B6 (D+), U1.111 (USB-DP)
USB_DEVICE-: J5.A7 (D-), J5.B7 (D-), U1.110 (USB-DM)
USER_LED0: D6.2 (A), U1.3 (PG2/SDC1_D0/PG_EINT2)
USER_LED1: D5.2 (A), U1.4 (PG1/SDC1_CMD/PG_EINT1)
VDD_RADIO_1: C18.2, C31.2, IC1.2 (VDD_IN), IC1.9 (VBAT_RF), IC1.10 (VBAT_DIO), L1.2, R1.1
VDD_RADIO_2: C19.2, C32.2, IC2.2 (VDD_IN), IC2.9 (VBAT_RF), IC2.10 (VBAT_DIO), L2.2, R2.1
X24MIN: C98.1, U1.75 (X24MIN), Y3.1 (X1)
X24MOUT: C102.1, U1.74 (X24MOUT), Y3.3 (X2)
X32KIN: C95.1, R29.1, U1.96 (X32KIN), Y2.2
X32KOUT: C91.1, R29.2, U1.95 (X32KOUT), Y2.1

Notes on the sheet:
ldo enable bağlancak
LED'S
3.3V FOR SX1250
SX1302
5V to 1.2V
5V to 3.3V
USB POWER
RF SHIELD
ETHERNET
SX1250
5V to 3V
ALLWINNER V3S
SD NAND
R18-R21 - вроде и без них Ethernet работает
GPS
DECOUPLING CAPACITORS
5V to 1.8V
